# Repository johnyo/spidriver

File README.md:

spidriver
=========

SPI, 8 Channel Switch Driver PCB

Designed as a daughter board for the Agilent L-Series Multiport Electromechanical Coaxial Switches

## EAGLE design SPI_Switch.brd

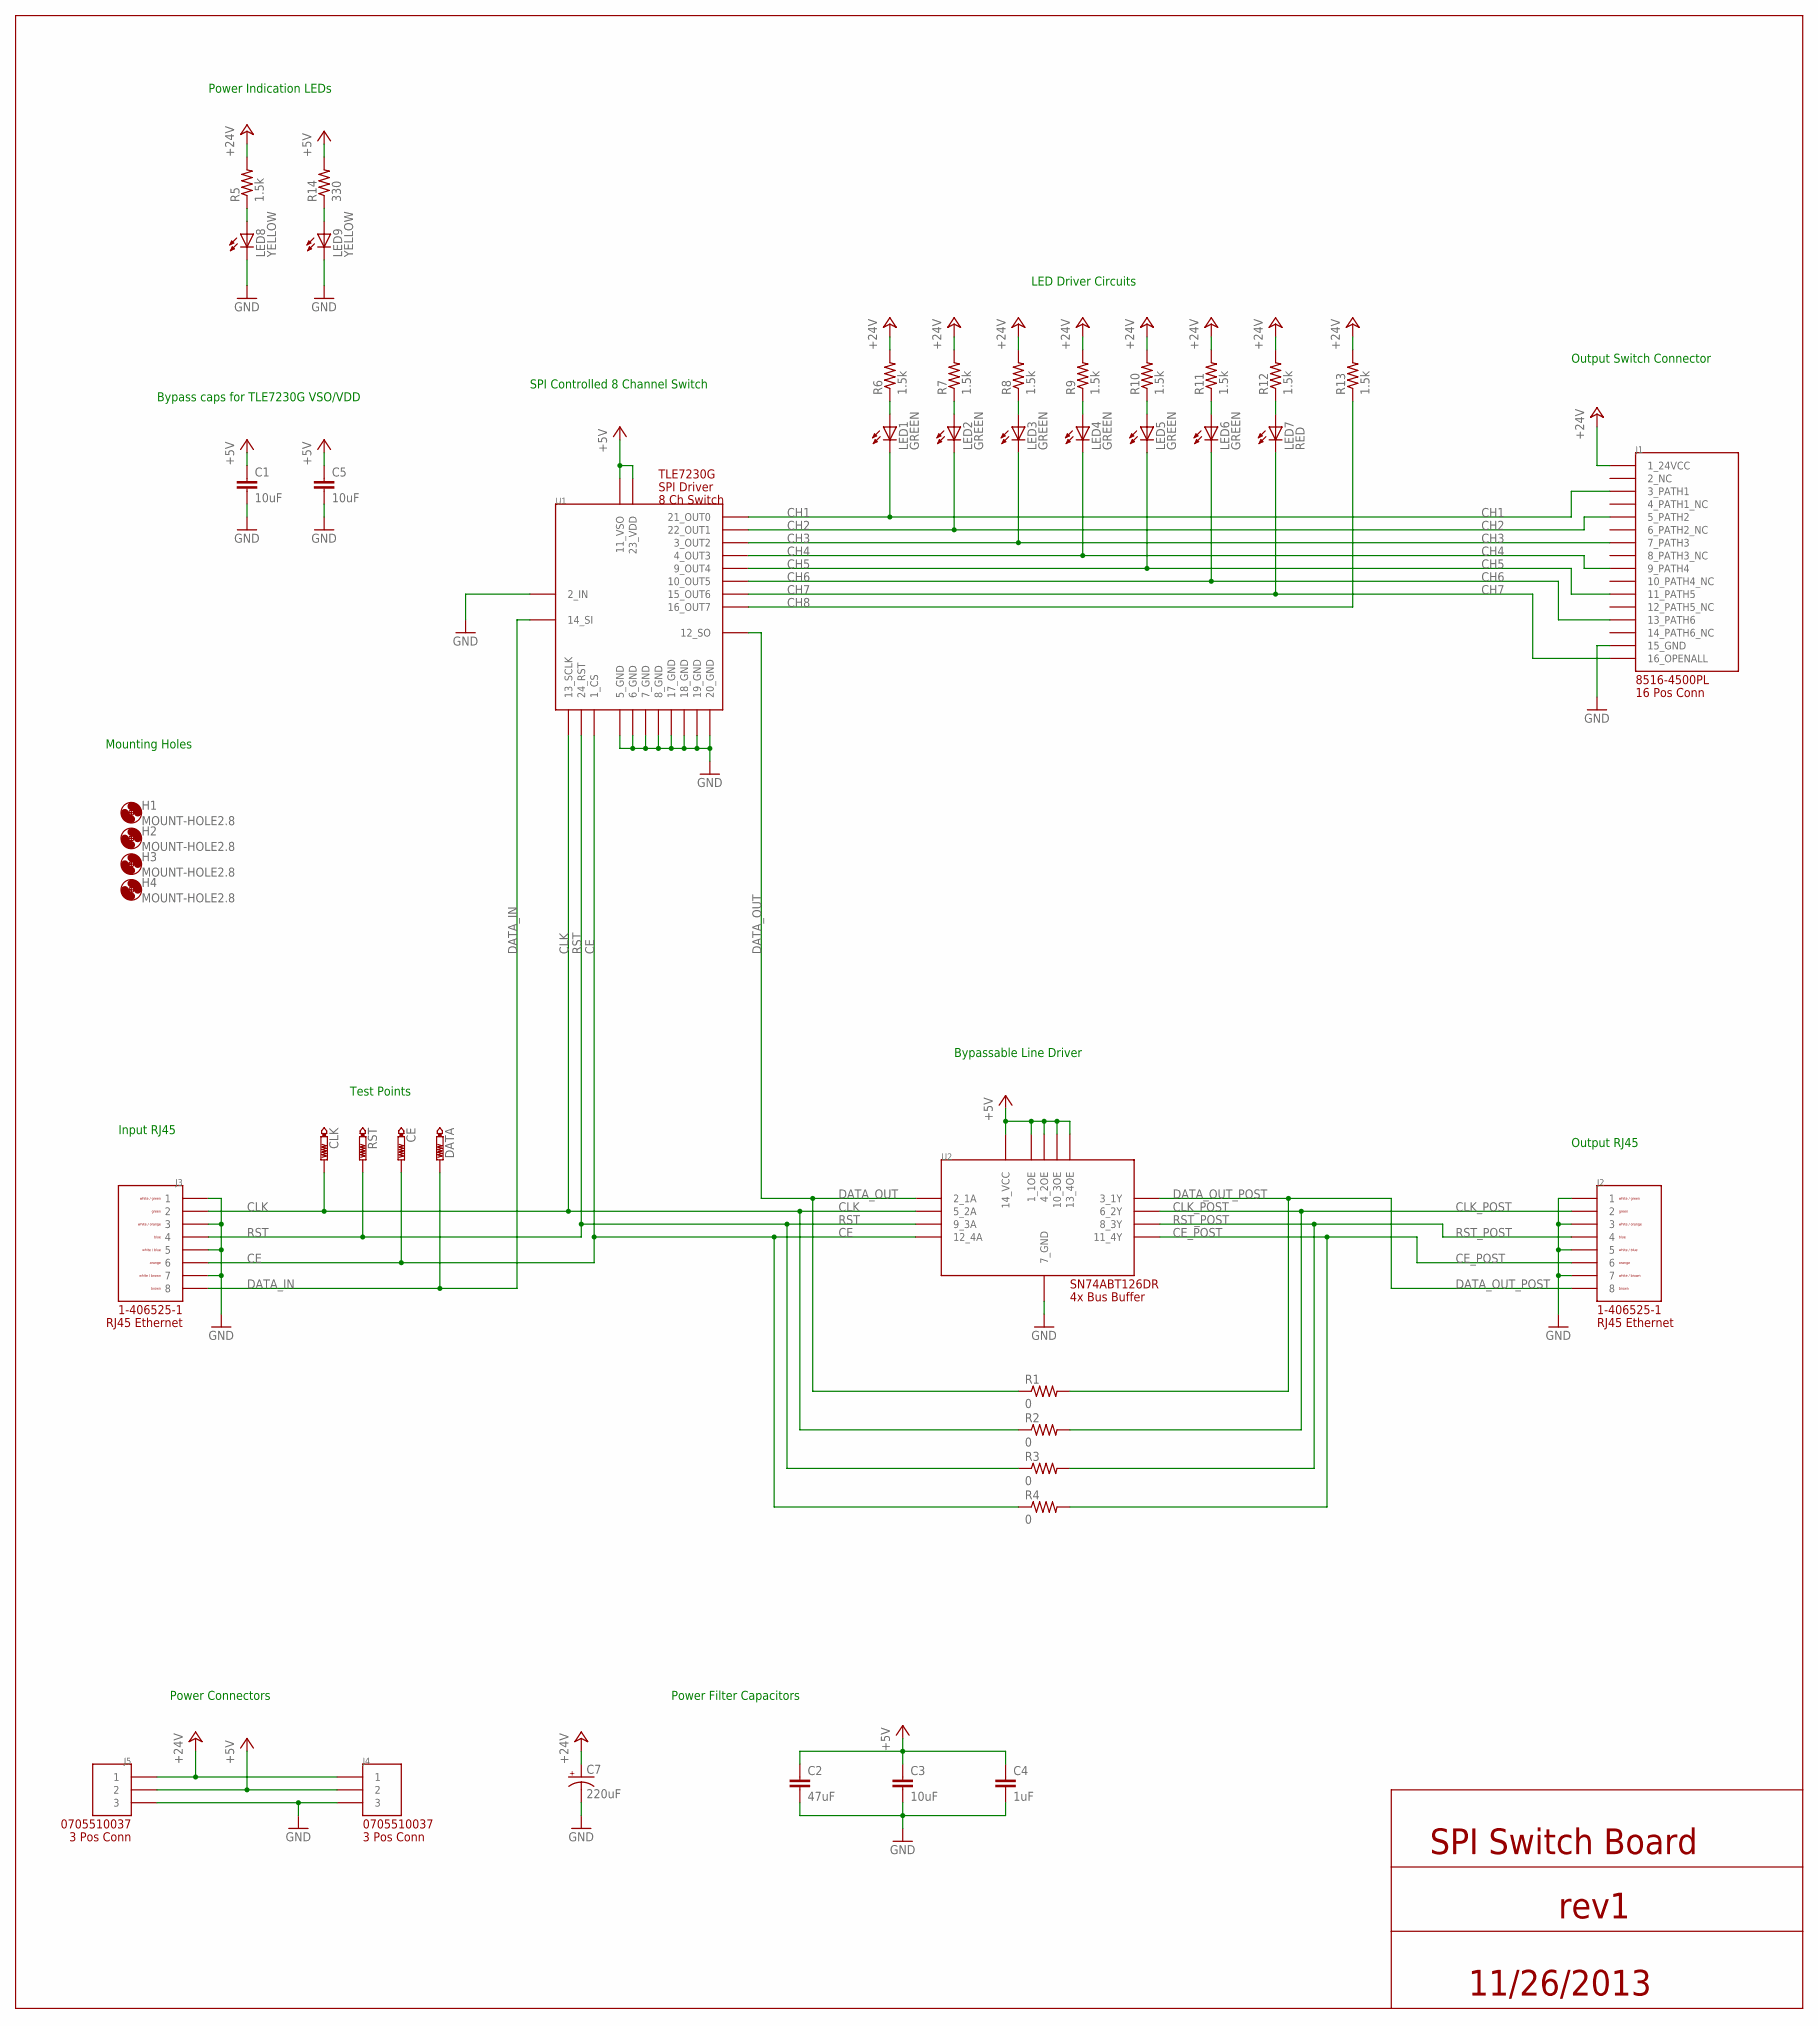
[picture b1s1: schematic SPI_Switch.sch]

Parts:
C1, C3, C5: 10uF; 0805
C2: 47uF; 0805
C4: 1uF; 0805
C7: 220uF; PANASONIC_E
CE: PTR1PAD1-13; P1-13
CLK: PTR1PAD1-13; P1-13
DATA: PTR1PAD1-13; P1-13
H1, H2, H3, H4: MOUNT-HOLE2.8; 2,8
J1: 8516-4500PL
J2, J3: 1-406525-1
J4, J5: 0705510037
LED1, LED2, LED3, LED4, LED5, LED6: GREEN; LED-1206
LED7: RED; LED-1206
LED8, LED9: YELLOW; LED-1206
R1, R2, R3, R4: 0; 0805
R5, R6, R7, R8, R9, R10, R11, R12, R13: 1.5k; 1206
R14: 330; 0805
RST: PTR1PAD1-13; P1-13
U1: TLE7230G
U2: SN74ABT126

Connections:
+5V: C1.1, C2.1, C3.1, C4.1, C5.1, J4.P$2 (2), J5.P$2 (2), R14.2, U1.11 (11_VSO), U1.23 (23_VDD), U2.1 (1_1OE), U2.4 (4_2OE), U2.10 (10_3OE), U2.13 (13_4OE), U2.14 (14_VCC)
+24V: C7.+, J1.P$1 (1_24VCC), J4.P$1 (1), J5.P$1 (1), R5.2, R6.2, R7.2, R8.2, R9.2, R10.2, R11.2, R12.2, R13.2
CE: CE.TP, J3.P$6 (6), R4.1, U1.1 (1_CS), U2.12 (12_4A)
CE_POST: J2.P$6 (6), R4.2, U2.11 (11_4Y)
CH1: J1.P$3 (3_PATH1), LED1.C, U1.21 (21_OUT0)
CH2: J1.P$5 (5_PATH2), LED2.C, U1.22 (22_OUT1)
CH3: J1.P$7 (7_PATH3), LED3.C, U1.3 (3_OUT2)
CH4: J1.P$9 (9_PATH4), LED4.C, U1.4 (4_OUT3)
CH5: J1.P$11 (11_PATH5), LED5.C, U1.9 (9_OUT4)
CH6: J1.P$13 (13_PATH6), LED6.C, U1.10 (10_OUT5)
CH7: J1.P$16 (16_OPENALL), LED7.C, U1.15 (15_OUT6)
CH8: R13.1, U1.16 (16_OUT7)
CLK: CLK.TP, J3.P$2 (2), R2.1, U1.13 (13_SCLK), U2.5 (5_2A)
CLK_POST: J2.P$2 (2), R2.2, U2.6 (6_2Y)
DATA_IN: DATA.TP, J3.P$8 (8), U1.14 (14_SI)
DATA_OUT: R1.1, U1.12 (12_SO), U2.2 (2_1A)
DATA_OUT_POST: J2.P$8 (8), R1.2, U2.3 (3_1Y)
GND: C1.2, C2.2, C3.2, C4.2, C5.2, C7.-, J1.P$15 (15_GND), J2.P$1 (1), J2.P$3 (3), J2.P$5 (5), J2.P$7 (7), J3.P$1 (1), J3.P$3 (3), J3.P$5 (5), J3.P$7 (7), J4.P$3 (3), J5.P$3 (3), LED8.C, LED9.C, U1.2 (2_IN), U1.5 (5_GND), U1.6 (6_GND), U1.7 (7_GND), U1.8 (8_GND), U1.17 (17_GND), U1.18 (18_GND), U1.19 (19_GND), U1.20 (20_GND), U2.7 (7_GND)
unnamed: LED1.A, R6.1
unnamed: LED8.A, R5.1
unnamed: LED2.A, R7.1
unnamed: LED9.A, R14.1
unnamed: LED3.A, R8.1
unnamed: LED4.A, R9.1
unnamed: LED5.A, R10.1
unnamed: LED6.A, R11.1
unnamed: LED7.A, R12.1
RST: J3.P$4 (4), R3.1, RST.TP, U1.24 (24_RST), U2.9 (9_3A)
RST_POST: J2.P$4 (4), R3.2, U2.8 (8_3Y)

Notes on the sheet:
Power Connectors
Power Filter Capacitors
Input RJ45
Test Points
SPI Controlled 8 Channel Switch
Bypassable Line Driver
Output RJ45
Bypass caps for TLE7230G VSO/VDD
SPI Switch Board
rev1
11/26/2013
LED Driver Circuits
Output Switch Connector
Power Indication LEDs
Mounting Holes

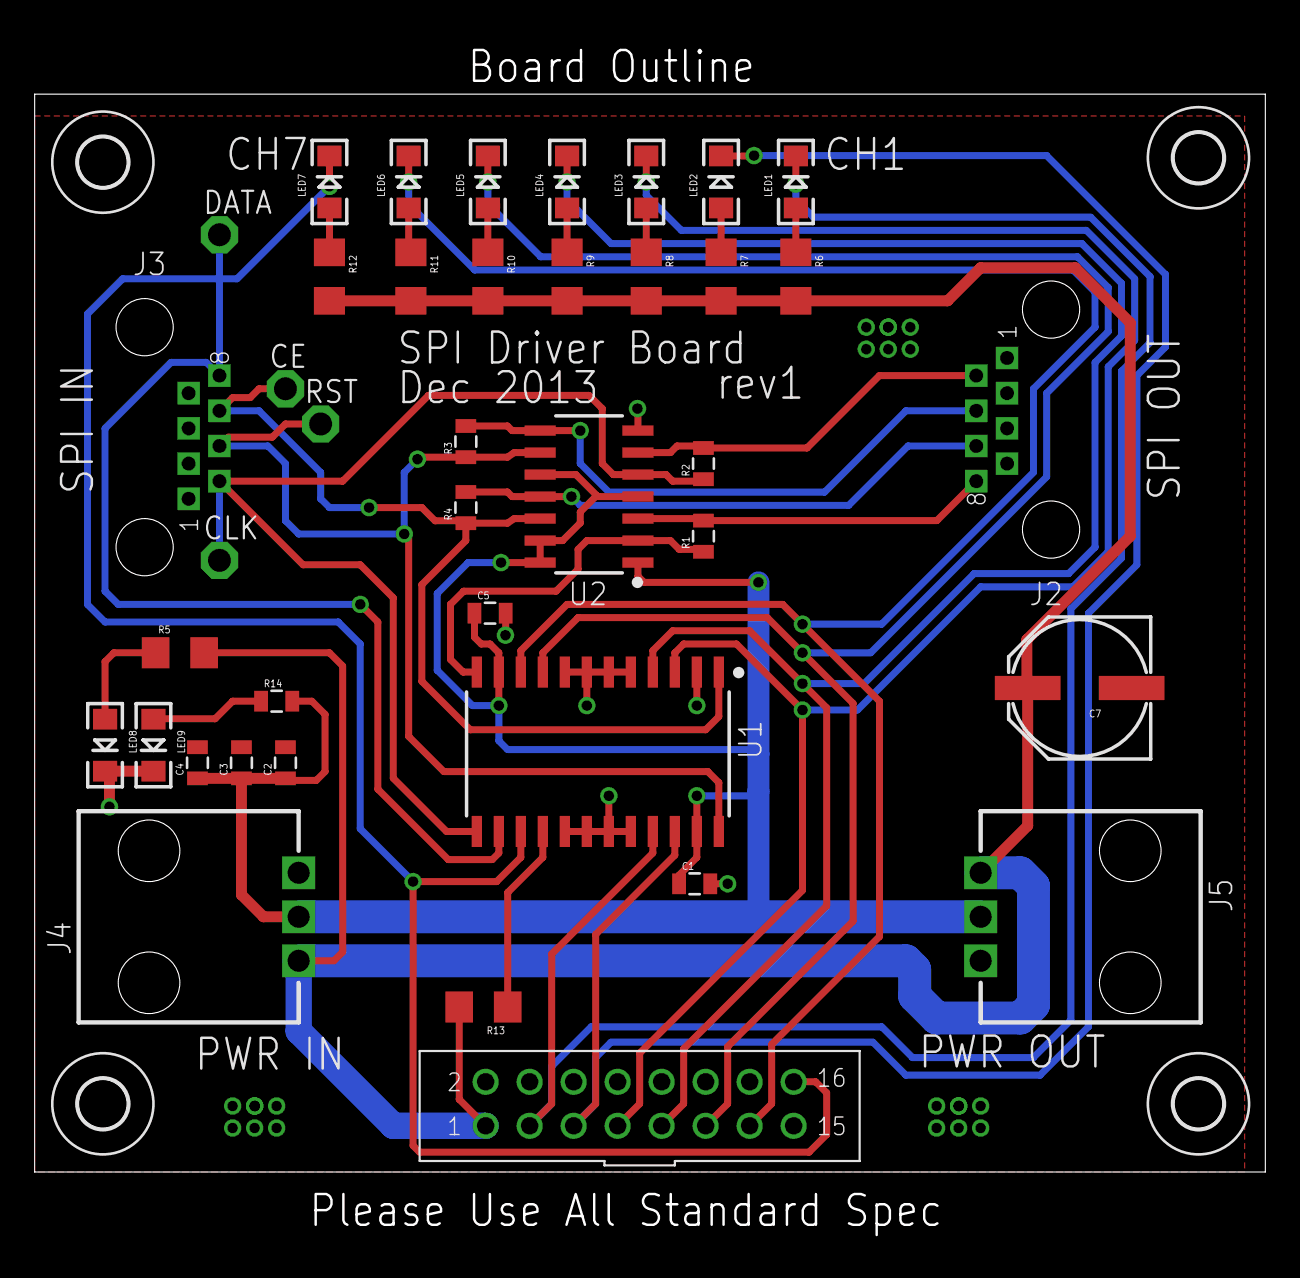
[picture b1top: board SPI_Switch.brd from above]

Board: 2 copper layers, 71.0 x 69.8 mm, 44 parts (1 on the bottom side), 29 nets.

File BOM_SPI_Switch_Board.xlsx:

BOM SPI Driver Board
 |  |  | DigiKey Web ID: | 49469585
 |  |  | DigiKey Access ID: | 57341
Reference | Value | Info | Footprint | Supplier Part Number | Manufacturer Part Number | Qty Per Board
C7 | 220 uF | Tantalum, 50V | CAP_POL | 493-6228-1-ND | UUR1H221MNL1GS | 1
C1, C3, C5 | 10 uF | Ceramic, 10V | 0805 (2012 Metric) | 311-1355-1-ND | CC0805ZKY5V6BB106 | 1
C2 | 47 uF | Ceramic, 10V | 0805 (2012 Metric) | 445-8239-1-ND | C2012X5R1A476M125AC | 1
C4 | 1 uF | Ceramic, 25V | 0805 (2012 Metric) | 311-1358-1-ND | CC0805ZRY5V8BB105 | 1
J4, J5 | N/A | Power Connector | 705510037 | WM7993-ND | '0705510037 | 2
J2, J3 | N/A | RJ45 Connector | 1-406525-1 | A102034-ND | 1-406525-1 | 2
U2 | N/A | Line Driver | SN74ABT126DR | 296-1020-1-ND | SN74ABT126DR | 1
U1 | N/A | SPI Driver | TLE7230G | TLE7230GCT-ND | TLE7230G | 1
J1 | N/A | Agilent Connector | 8516-4500PL | MSPV16-ND | 8516-4500PL | 1
R1, R2, R3, R4 | 0 Ohm | Jumper | 0805 (2012 Metric) | P0.0ACT-ND | ERJ-6GEY0R00V | 4
LED1, LED2, LED3, LED4, LED5, LED6 | 2.1 V, 20 mA | Green LED | 1206 (3216 Metric) | 1080-1419-1-ND | QTLP650D4TR | 6
LED7 | 2.1 V, 20 mA | Red LED | 1206 (3216 Metric) | 516-1440-1-ND | HSMS-C150 | 1
LED8, LED9 | 2.1 V, 20 mA | Yellow LED | 1206 (3216 Metric) | 516-1442-1-ND | HSMY-C150 | 2
R5, R6, R7, R8, R9, R10, R11, R12, R13 | 1.5k Ohm | 0.5W Resistor | 1206 (3216 Metric) | RNCP1206FTD1K50CT-ND | RNCP1206FTD1K50 | 9
R14 | 330 Ohm | 1/4W Resistor | 0805 (2012 Metric) | RHM1215CT-ND | LTR10EZPF3300 | 1

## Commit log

2013-11-26 updated library parts for easier schematic
2013-11-26 added stuff
2013-11-26 finished first take
2013-11-26 Cleaned up schematic by bringing everything closer together, added PDF
2013-12-01 adding daniel's changes
2013-12-02 Adding part numbers
2013-12-02 finished BOM
2013-12-02 preliminary layout
2013-12-02 Finished layout, must do routing now
2013-12-02 Added channel routings
2013-12-02 moved some parts to make layout for power cleaner
2013-12-03 about to route lights. have lined up everything so that channels can easily be routed to LEDs
2013-12-03 finished fanning out LEDs
2013-12-03 finished routing except decoupling caps
2013-12-03 Finished routing except ground plane
2013-12-03 debugging drc errors
2013-12-03 4 airwires left
2013-12-03 Created fabrication outpute, this is the version I sent to Daniel on Dec 3rd
2013-12-03 added dimensions
2013-12-03 Replaced decoupling caps for line driver with a larger package. Added smaller resistors for LEDs. Must ensure we never pull over 20mA with this resistor package.
2013-12-05 redoing layout
2013-12-05 Redid layout again get rid of data out crossing 5V. Time to re-route.
2013-12-05 re routed outputs and LEDs
2013-12-05 finished take 2
2013-12-05 finished the second go at rev1
2013-12-06 Switched the footprint for R5 to be smaller
2013-12-06 Fixed Typo

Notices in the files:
parts and their libraries:
SparkFun-Passives: Licensing: CC v3.0 Share-Alike You are welcome to use this library for commercial purposes.
